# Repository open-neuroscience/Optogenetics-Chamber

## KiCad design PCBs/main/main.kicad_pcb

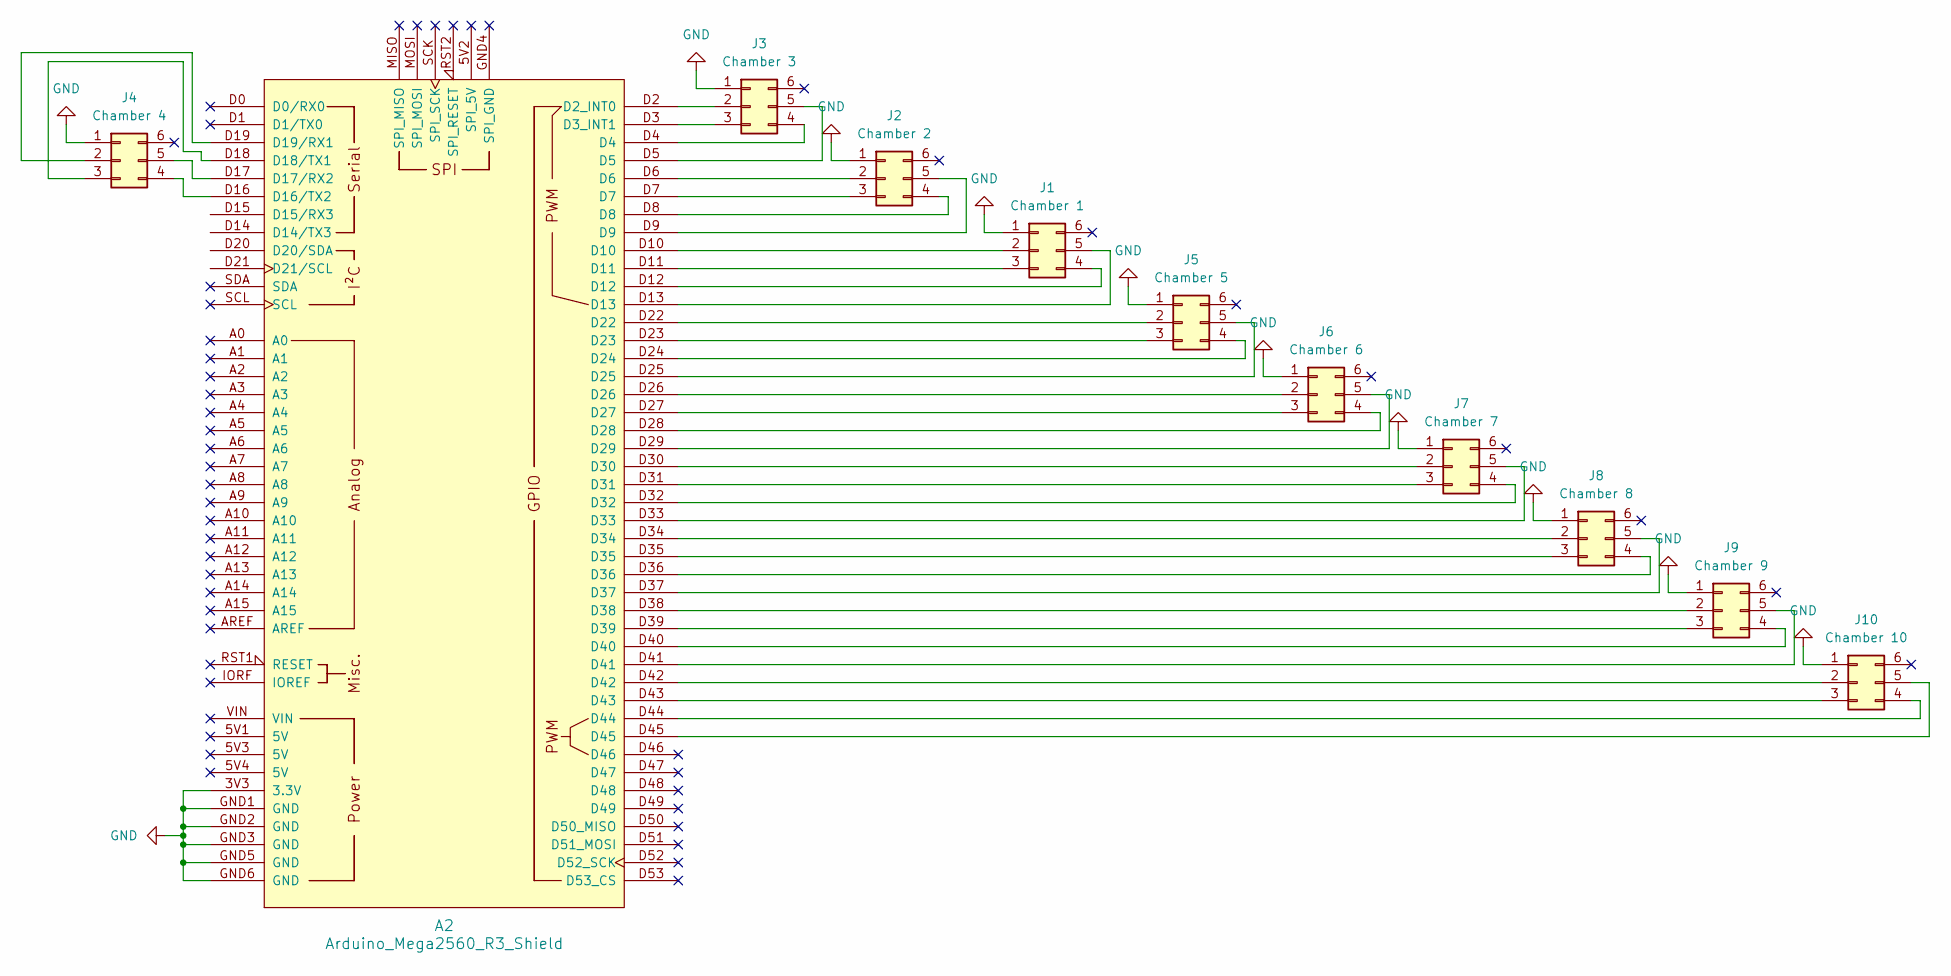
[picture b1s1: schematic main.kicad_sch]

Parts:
A2: Arduino_Mega2560_R3_Shield
J1: Chamber 1; IDC-Header_2x03_P2.54mm_Vertical
J2: Chamber 2; IDC-Header_2x03_P2.54mm_Vertical
J3: Chamber 3; IDC-Header_2x03_P2.54mm_Vertical
J4: Chamber 4; IDC-Header_2x03_P2.54mm_Vertical
J5: Chamber 5; IDC-Header_2x03_P2.54mm_Vertical
J6: Chamber 6; IDC-Header_2x03_P2.54mm_Vertical
J7: Chamber 7; IDC-Header_2x03_P2.54mm_Vertical
J8: Chamber 8; IDC-Header_2x03_P2.54mm_Vertical
J9: Chamber 9; IDC-Header_2x03_P2.54mm_Vertical
J10: Chamber 10; IDC-Header_2x03_P2.54mm_Vertical

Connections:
GND: A2.3V3 (3.3V), A2.GND1 (GND), A2.GND2 (GND), A2.GND3 (GND), A2.GND5 (GND), A2.GND6 (GND), J1.1, J2.1, J3.1, J4.1, J5.1, J6.1, J7.1, J8.1, J9.1, J10.1
unnamed: A2.D2 (D2_INT0), J3.2
unnamed: A2.D3 (D3_INT1), J3.3
unnamed: A2.D16 (D16/TX2), J4.4
unnamed: A2.D17 (D17/RX2), J4.5
unnamed: A2.D18 (D18/TX1), J4.3
unnamed: A2.D19 (D19/RX1), J4.2
unnamed: A2.D10, J1.2
unnamed: A2.D11, J1.3
unnamed: A2.D12, J1.4
unnamed: A2.D13, J1.5
unnamed: A2.D6, J2.2
unnamed: A2.D7, J2.3
unnamed: A2.D8, J2.4
unnamed: A2.D9, J2.5
unnamed: A2.D4, J3.4
unnamed: A2.D5, J3.5
unnamed: A2.D22, J5.2
unnamed: A2.D23, J5.3
unnamed: A2.D24, J5.4
unnamed: A2.D25, J5.5
unnamed: A2.D26, J6.2
unnamed: A2.D27, J6.3
unnamed: A2.D28, J6.4
unnamed: A2.D29, J6.5
unnamed: A2.D30, J7.2
unnamed: A2.D31, J7.3
unnamed: A2.D32, J7.4
unnamed: A2.D33, J7.5
unnamed: A2.D34, J8.2
unnamed: A2.D35, J8.3
unnamed: A2.D36, J8.4
unnamed: A2.D37, J8.5
unnamed: A2.D38, J9.2
unnamed: A2.D39, J9.3
unnamed: A2.D40, J9.4
unnamed: A2.D41, J9.5
unnamed: A2.D42, J10.2
unnamed: A2.D43, J10.3
unnamed: A2.D44, J10.4
unnamed: A2.D45, J10.5

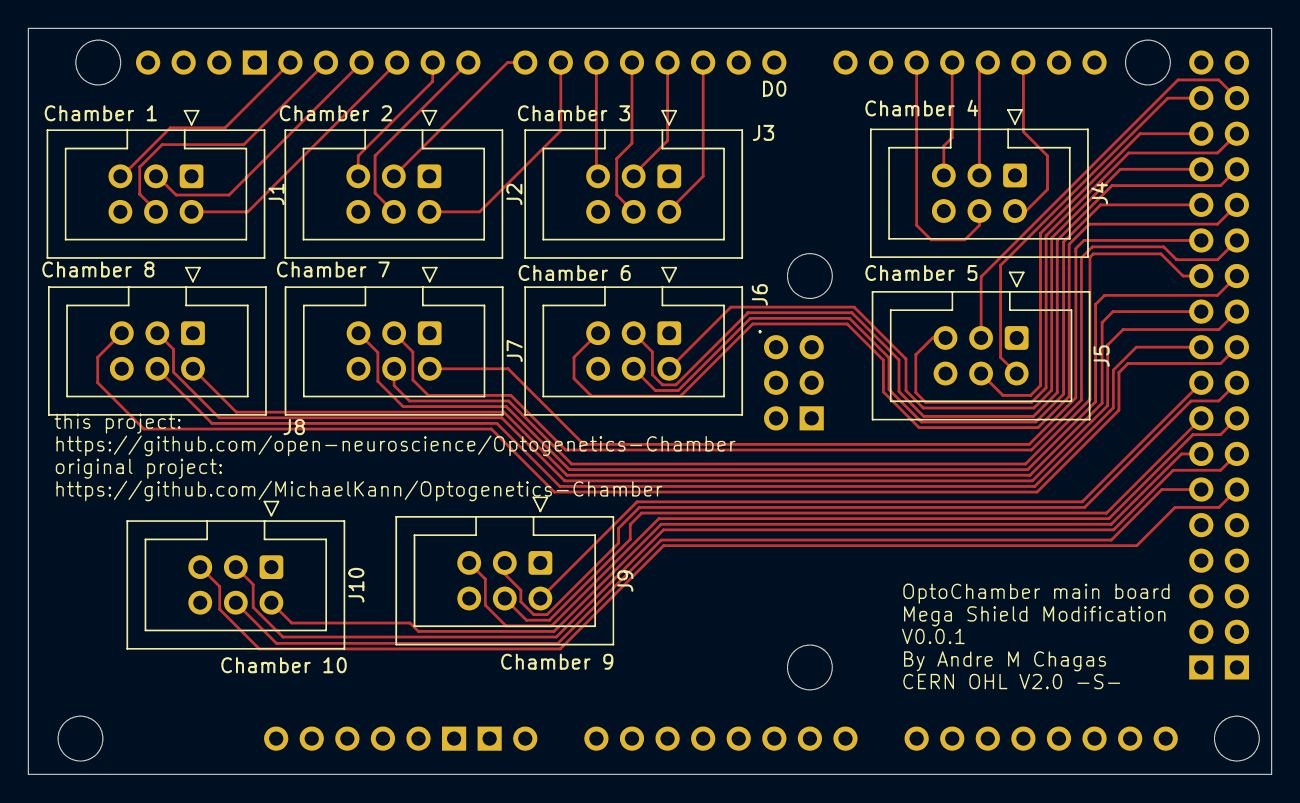
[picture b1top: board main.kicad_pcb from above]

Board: 2 copper layers, 88.8 x 53.2 mm, 11 parts (0 on the bottom side), 41 nets.

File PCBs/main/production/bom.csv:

Designator,Footprint,Quantity,Value,LCSC Part #
A2,Arduino_Mega2560_R3_Shield,1,Arduino_Mega2560_R3_Shield,
J1,IDC-Header_2x03_P2.54mm_Vertical,1,Chamber 1,
J10,IDC-Header_2x03_P2.54mm_Vertical,1,Chamber 10,
J2,IDC-Header_2x03_P2.54mm_Vertical,1,Chamber 2,
J3,IDC-Header_2x03_P2.54mm_Vertical,1,Chamber 3,
J4,IDC-Header_2x03_P2.54mm_Vertical,1,Chamber 4,
J5,IDC-Header_2x03_P2.54mm_Vertical,1,Chamber 5,
J6,IDC-Header_2x03_P2.54mm_Vertical,1,Chamber 6,
J7,IDC-Header_2x03_P2.54mm_Vertical,1,Chamber 7,
J8,IDC-Header_2x03_P2.54mm_Vertical,1,Chamber 8,
J9,IDC-Header_2x03_P2.54mm_Vertical,1,Chamber 9,

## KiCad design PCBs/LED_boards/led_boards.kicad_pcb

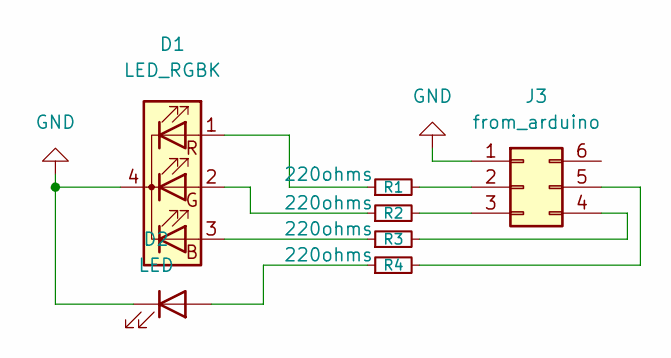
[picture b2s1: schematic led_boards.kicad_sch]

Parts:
D1: LED_RGBK; LED_D5.0mm-4_RGB_Wide_Pins
D2: LED; LED_D5.0mm_Clear
J3: from_arduino; IDC-Header_2x03_P2.54mm_Vertical
R1, R2, R3, R4: 220ohms; R_Axial_DIN0309_L9.0mm_D3.2mm_P12.70mm_Horizontal

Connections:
GND: D1.4 (K), D2.1 (K), J3.1
unnamed: D1.3 (BA), R3.1
unnamed: D1.2 (GA), R2.1
unnamed: D1.1 (RA), R1.1
unnamed: D2.2 (A), R4.1
unnamed: J3.2, R1.2
unnamed: J3.3, R2.2
unnamed: J3.4, R3.2
unnamed: J3.5, R4.2

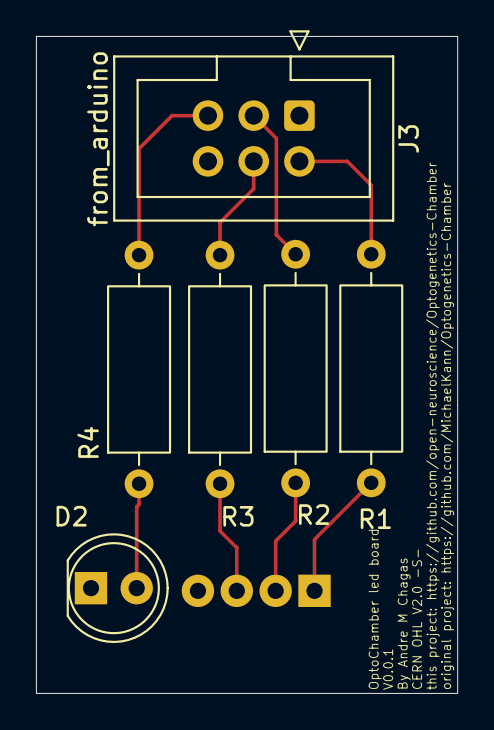
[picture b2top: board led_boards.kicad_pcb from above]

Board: 2 copper layers, 23.4 x 36.5 mm, 7 parts (1 on the bottom side), 9 nets.

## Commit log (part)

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2026-06-22 start creating arduino mega shield and bill of materials
2026-06-22 update bill of materials
2026-06-24 add cost for the mega board PCB shield
2026-06-24 work on first prototype for the boards
2026-06-25 create parts for 3D printing
2026-06-26 update bom and finish first version of PCBs
2026-06-26 last save after production board was made

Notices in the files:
PCBs/LED_boards/led_boards.kicad_pcb:
CERN OHL V2.0 -S-
